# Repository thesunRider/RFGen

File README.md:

# RFGen

This is an open source DIY Square wave generator. There are two versions included: 
- Blue pill - (1Hz - 960Mhz)
- Atmega328p/Arduino (1Hz - 250Mhz)

### Schematics:

Arduino version

Bluepill version

- Si5351 - Channel A,B (1Khz - 250Mhz)
- CMT2119A - Channel E (only for bluepill version: 250Mhz - 960Mhz)

# Demo

Demo Video 

https://github.com/user-attachments/assets/bd40d5bd-5a4e-4a5a-9730-a542df9f6650

# Installation

- Upload 328p schematics for an Arduino based generator.
- Upload bluepill schematic for Bluepilll based generator.

> Gerber files attatched with kicad designs

# Usage

There is a bias tee included for these channels whose bias can be adjusted by the attached external potentiometer. 

Supply 9V on the power input, this is regulated to 5v by l7805

# Development

To program a soldered bluepill via USB kindly power off the device before connecting the USB. SInce UART pins are exposed you can program it via those headers too.

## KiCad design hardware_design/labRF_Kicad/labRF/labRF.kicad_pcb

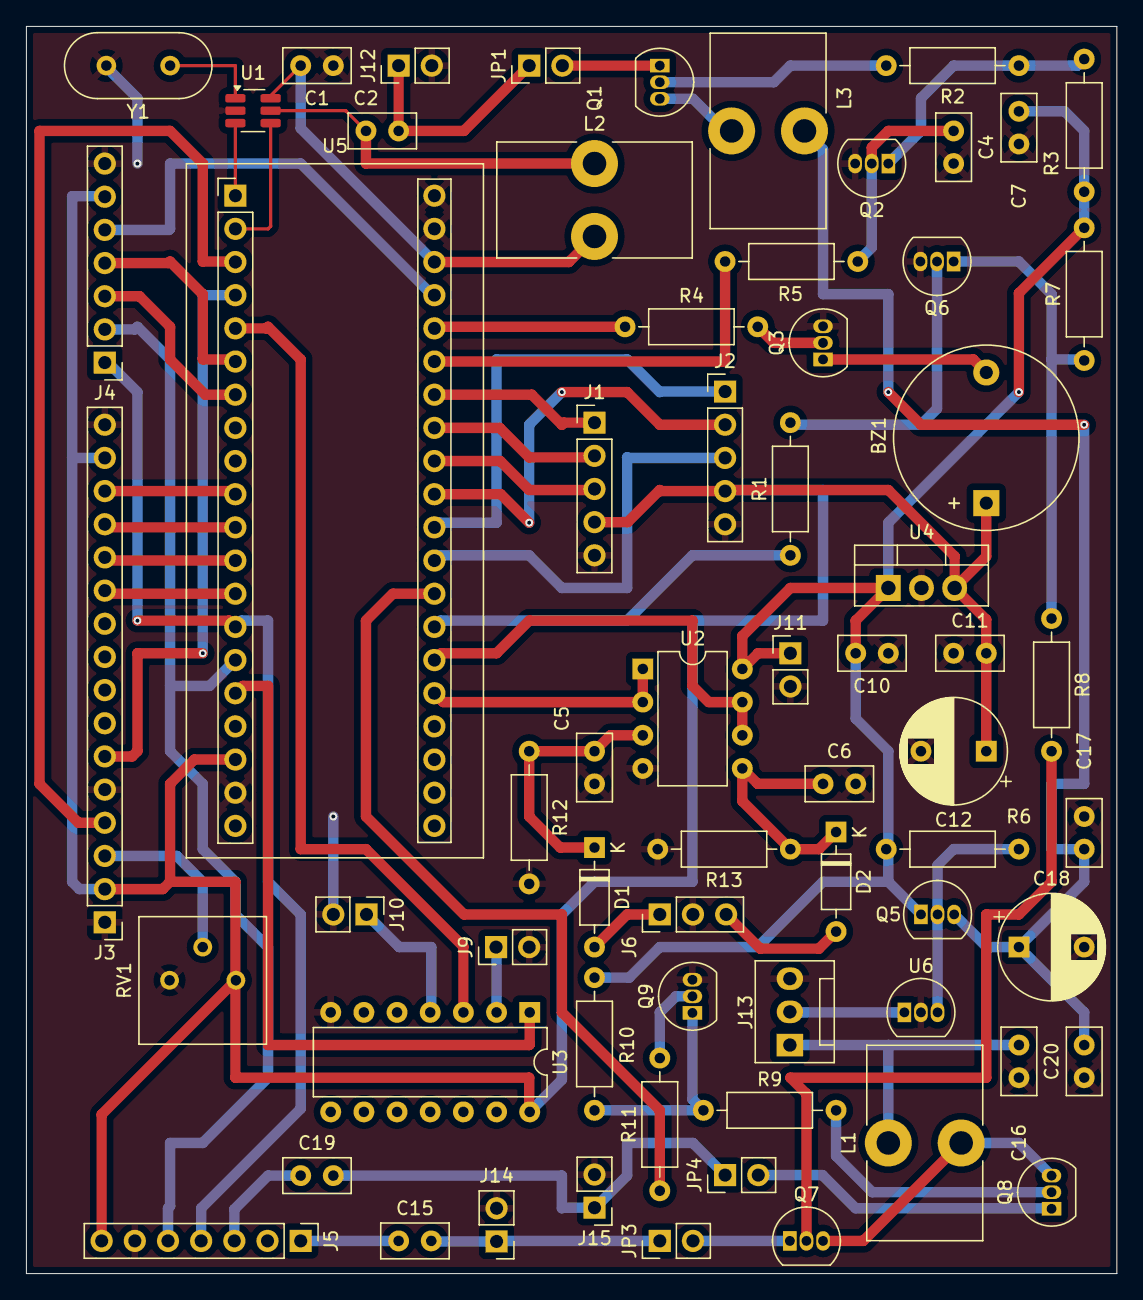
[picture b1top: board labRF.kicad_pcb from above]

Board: 2 copper layers, 83.5 x 95.5 mm, 66 parts (0 on the bottom side), 64 nets.

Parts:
BZ1: Buzzer; Buzzer_D14mm_H7mm_P10mm
C1, C2, C7, C11, C15, C16, C19: 100n; C_Disc_D5.0mm_W2.5mm_P2.50mm
C4, C5, C6, C10, C17, C20: 10n; C_Disc_D5.0mm_W2.5mm_P2.50mm
C12, C18: 100u; CP_Radial_D8.0mm_P5.00mm
D1, D2: 1N4148; D_DO-35_SOD27_P7.62mm_Horizontal
J1: select_rotary; PinHeader_1x05_P2.54mm_Vertical
J2: mode_rotary; PinHeader_1x05_P2.54mm_Vertical
J3: lcd_socket; PinHeader_1x16_P2.54mm_Vertical
J4: comms; PinHeader_1x07_P2.54mm_Vertical
J5: si5351; PinHeader_1x07_P2.54mm_Vertical
J6: Conn_01x03_Socket; PinHeader_1x03_P2.54mm_Vertical
J9: pwmD; PinHeader_1x02_P2.54mm_Vertical
J10: pwmC; PinHeader_1x02_P2.54mm_Vertical
J11: pwrIn; PinHeader_1x02_P2.54mm_Vertical
J12, J15: clk2; PinHeader_1x02_P2.54mm_Vertical
J13: bias_pot; FanPinHeader_1x03_P2.54mm_Vertical
J14: clk0; PinHeader_1x02_P2.54mm_Vertical
JP1, JP3, JP4: Jumper_2_Open; PinHeader_1x02_P2.54mm_Vertical
L1, L3: 100u; L_Toroid_Vertical_L14.7mm_W8.6mm_P5.58mm_Pulse_KM-1
L2: 200n; L_Toroid_Vertical_L14.7mm_W8.6mm_P5.58mm_Pulse_KM-1
Q1, Q7, Q8: BC557; TO-92_Inline
Q2, Q3, Q5, Q6, Q9: BC547; TO-92_Inline
R1, R2, R5, R8, R9, R11: 10k; R_Axial_DIN0207_L6.3mm_D2.5mm_P10.16mm_Horizontal
R3, R6, R7, R10: 1k; R_Axial_DIN0207_L6.3mm_D2.5mm_P10.16mm_Horizontal
R4: 2.2k; R_Axial_DIN0207_L6.3mm_D2.5mm_P10.16mm_Horizontal
R12, R13: 100k; R_Axial_DIN0207_L6.3mm_D2.5mm_P10.16mm_Horizontal
RV1: R_Potentiometer; Potentiometer_Bourns_3386P_Vertical
U1: CMT2119; SOT-23-6_Handsoldering
U2: LM358; DIP-8_W7.62mm
U3: 74HC04; DIP-14_W7.62mm
U4: L7805; TO-220-3_Vertical
U5: YAAJ_BluePill; YAAJ_BluePill_2
U6: TL431LP; TO-92_Inline
Y1: 26Mhz; Crystal_HC49-U_Vertical

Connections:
+3V3: C1.2, L2.2, U1.6 (VDD), U5.38 (3V3)
+5V: BZ1.1 (+), C11.2, C12.1, J1.4, J2.4, J3.2, J3.15, J4.6, J5.7, RV1.1, U3.14 (VCC), U4.3 (OUT), U5.18 (5V)
+9V: C7.2, C10.2, J11.1, Q5.1 (C), R3.2, R6.2, R7.2, R10.2, U2.8 (V+), U4.1 (IN)
GND: C1.1, C4.2, C5.2, C6.2, C7.1, C10.1, C11.1, C12.2, C16.1, C17.1, C18.2, C20.1, J1.5, J2.5, J3.1, J3.5, J3.16, J4.7, J5.6, J6.2, J9.2, J10.2, J11.2, J12.2, J13.3, J14.2, J15.2, Q2.3 (E), Q3.3 (E), Q6.3 (E), Q9.3 (E), R12.2, R13.2, RV1.3, U1.2 (GND), U2.4 (V-), U3.7 (GND), U4.2 (GND), U5.19 (GND), U5.39 (GND), U5.40 (GND), U6.2 (A), Y1.2
unnamed: BZ1.2 (-), Q3.1 (C)
unnamed: D1.2 (A), J6.1
unnamed: C5.1, D1.1 (K), R12.1, U2.3 (+)
unnamed: D2.2 (A), J6.3
unnamed: C6.1, D2.1 (K), R13.1, U2.5 (+)
unnamed: J9.1, U3.2
unnamed: J10.1, U3.4
unnamed: C2.2, J12.1, JP1.1 (A)
unnamed: C16.2, C17.2, C18.1, C20.2, J13.1, L1.1, L3.1, Q5.3 (E)
unnamed: J13.2, U6.1 (REF)
unnamed: C15.2, J14.1, JP3.1 (A)
unnamed: C19.2, J15.1, JP4.1 (A)
unnamed: JP1.2 (B), Q1.1 (C)
unnamed: JP3.2 (B), Q7.1 (C)
unnamed: JP4.2 (B), Q8.1 (C)
unnamed: Q1.2 (B), R2.2
unnamed: L3.2, Q1.3 (E)
unnamed: C4.1, Q2.2 (B), R5.2
unnamed: Q2.1 (C), R2.1, R3.1
unnamed: Q3.2 (B), R4.2
unnamed: Q5.2 (B), R6.1, U6.3 (K)
unnamed: Q6.2 (B), R1.2
unnamed: Q6.1 (C), R7.1, R8.1
unnamed: Q7.2 (B), R8.2
unnamed: L1.2, Q7.3 (E), Q8.3 (E)
unnamed: Q8.2 (B), R9.2
unnamed: Q9.2 (B), R11.2
unnamed: Q9.1 (C), R9.1, R10.1
unnamed: U1.1 (XTAL), Y1.1
adc1: U2.6 (-), U2.7, U5.26 (PA1)
adc2: U2.1, U2.2 (-), U5.25 (PA0)
bias1: R1.1, U5.27 (PA2)
bias2: R11.1, U5.28 (PA3)
bias3: R5.1, U5.35 (PB10)
buzz: R4.1, U5.36 (PB11)
chanE: C2.1, L2.1, U1.5 (RFO)
chanc: U3.3, U5.5 (PA8)
chand: U3.1, U5.16 (PB8)
clk0: C15.1, J5.1
clk2: C19.1, J5.3
lcd_D4: J3.11, U5.13 (PB5)
lcd_D5: J3.12, U5.12 (PB4)
lcd_D6: J3.13, U5.11 (PB3)
lcd_D7: J3.14, U5.10 (PA15)
lcd_contrast: J3.3, RV1.2
lcd_enb: J3.6, U5.4 (PB15)
lcd_rs: J3.4, U5.3 (PB14)
reset: J4.5, U5.37 (RST)
rotm_clk: J2.1, U5.30 (PA5)
rotm_dt: J2.2, U5.31 (PA6)
rotm_sw: J2.3, U5.29 (PA4)
rots_clk: J1.1, U5.34 (PB1)
rots_dt: J1.2, U5.33 (PB0)
rots_sw: J1.3, U5.32 (PA7)
rx: J4.3, U5.7 (PA10)
scl: J4.1, J5.4, U5.14 (PB6)
sda: J4.2, J5.5, U5.15 (PB7)
twi_clk: U1.4 (CLK), U5.2 (PB13)
twi_data: U1.3 (DATA), U5.1 (PB12)
tx: J4.4, U5.6 (PA9)

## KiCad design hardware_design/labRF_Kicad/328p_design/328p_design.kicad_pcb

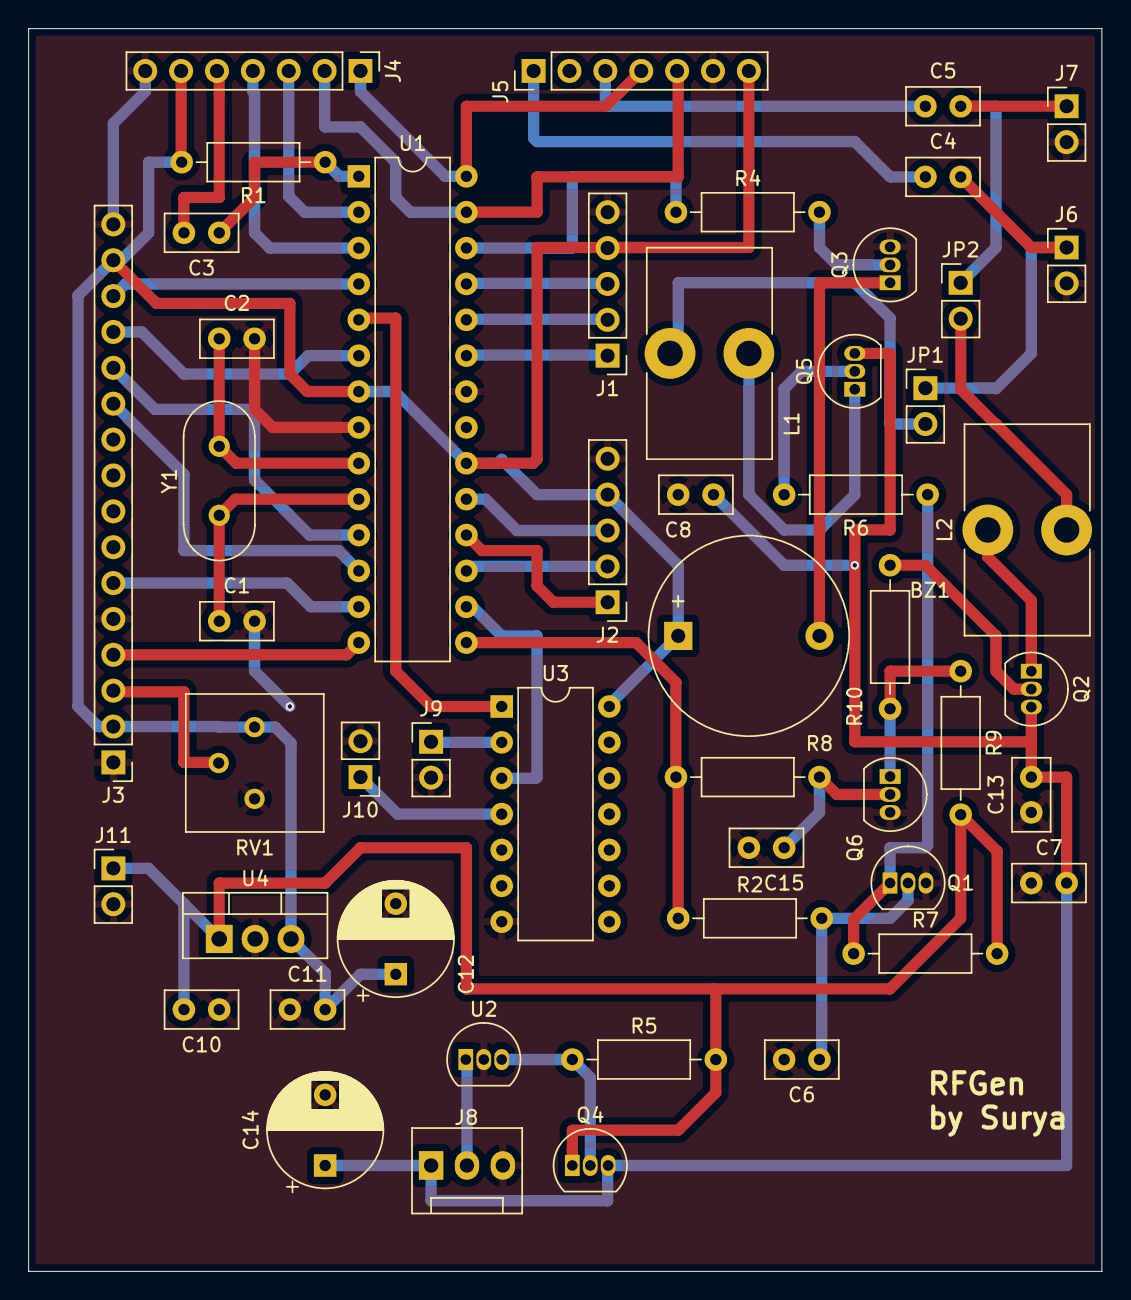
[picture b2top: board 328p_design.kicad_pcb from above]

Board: 2 copper layers, 76.0 x 88.0 mm, 51 parts (0 on the bottom side), 49 nets.

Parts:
BZ1: Buzzer; Buzzer_D14mm_H7mm_P10mm
C1, C2: 22p; C_Disc_D5.0mm_W2.5mm_P2.50mm
C3, C4, C5, C11, C13: 100n; C_Disc_D5.0mm_W2.5mm_P2.50mm
C6, C7, C8, C10, C15: 10n; C_Disc_D5.0mm_W2.5mm_P2.50mm
C12, C14: 100u; CP_Radial_D8.0mm_P5.00mm
J1: select_rotary; PinHeader_1x05_P2.54mm_Vertical
J2: mode_rotary; PinHeader_1x05_P2.54mm_Vertical
J3: lcd_socket; PinHeader_1x16_P2.54mm_Vertical
J4: comms; PinHeader_1x07_P2.54mm_Vertical
J5: si5351; PinHeader_1x07_P2.54mm_Vertical
J6: clk0; PinHeader_1x02_P2.54mm_Vertical
J7: clk2; PinHeader_1x02_P2.54mm_Vertical
J8: bias_pot; FanPinHeader_1x03_P2.54mm_Vertical
J9: pwmD; PinHeader_1x02_P2.54mm_Vertical
J10: pwmC; PinHeader_1x02_P2.54mm_Vertical
J11: pwrIn; PinHeader_1x02_P2.54mm_Vertical
JP1, JP2: Jumper_2_Open; PinHeader_1x02_P2.54mm_Vertical
L1, L2: 100u; L_Toroid_Vertical_L14.7mm_W8.6mm_P5.58mm_Pulse_KM-1
Q1, Q3, Q4, Q6: BC547; TO-92_Inline
Q2, Q5: BC557; TO-92_Inline
R1, R2, R6, R8, R10: 10k; R_Axial_DIN0207_L6.3mm_D2.5mm_P10.16mm_Horizontal
R4: 2.2k; R_Axial_DIN0207_L6.3mm_D2.5mm_P10.16mm_Horizontal
R5, R7, R9: 1k; R_Axial_DIN0207_L6.3mm_D2.5mm_P10.16mm_Horizontal
RV1: R_Potentiometer; Potentiometer_Bourns_3386P_Vertical
U1: ATmega328-P; DIP-28_W7.62mm
U2: TL431LP; TO-92_Inline
U3: 74HC04; DIP-14_W7.62mm
U4: L7805; TO-220-3_Vertical
Y1: 20Mhz; Crystal_HC49-U_Vertical

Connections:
+5V: BZ1.1 (+), C11.2, C12.1, J1.4, J2.4, J3.2, J3.15, J4.6, J5.7, R1.2, RV1.1, U1.7 (VCC), U1.20 (AVCC), U3.14 (VCC), U4.3 (OUT)
+9V: C10.2, J11.1, Q4.1 (C), R5.2, R7.2, R9.2, U4.1 (IN)
GND: C1.2, C2.2, C6.2, C7.1, C8.1, C10.1, C11.1, C12.2, C13.1, C14.2, C15.2, J1.5, J2.5, J3.1, J3.5, J3.16, J4.7, J5.6, J6.2, J7.2, J8.3, J9.2, J10.2, J11.2, Q1.3 (E), Q3.3 (E), Q6.3 (E), RV1.3, U1.8 (GND), U1.22 (GND), U2.2 (A), U3.7 (GND), U4.2 (GND)
unnamed: BZ1.2 (-), Q3.1 (C)
unnamed: C4.2, J6.1, JP1.1 (A)
unnamed: C5.2, J7.1, JP2.1 (A)
unnamed: C7.2, C8.2, C13.2, C14.1, J8.1, Q2.3 (E), Q4.3 (E), Q5.3 (E)
unnamed: J8.2, U2.1 (REF)
unnamed: J9.1, U3.2
unnamed: J10.1, U3.4
unnamed: JP1.2 (B), L1.2
unnamed: JP2.2 (B), L2.2
unnamed: C6.1, Q1.2 (B), R2.2
unnamed: Q1.1 (C), R6.1, R7.1
unnamed: Q2.2 (B), R10.2
unnamed: L2.1, Q2.1 (C)
unnamed: Q3.2 (B), R4.2
unnamed: Q4.2 (B), R5.1, U2.3 (K)
unnamed: Q5.2 (B), R6.2
unnamed: L1.1, Q5.1 (C)
unnamed: C15.1, Q6.2 (B), R8.2
unnamed: Q6.1 (C), R9.1, R10.1
unnamed: C2.1, U1.9 (XTAL1/PB6), Y1.2
unnamed: C1.1, U1.10 (XTAL2/PB7), Y1.1
unnamed: C3.1, R1.1, U1.1 (~RESET/PC6)
bias: R2.1, R8.1, U1.15 (PB1)
buzz: R4.1, U1.26 (PC3)
chanc: U1.16 (PB2), U3.3
chand: U1.5 (PD3), U3.1
clk0: C4.1, J5.1
clk2: C5.1, J5.3
lcd_D4: J3.11, U1.12 (PD6)
lcd_D5: J3.12, U1.11 (PD5)
lcd_D6: J3.13, U1.6 (PD4)
lcd_D7: J3.14, U1.4 (PD2)
lcd_contrast: J3.3, RV1.2
lcd_enb: J3.6, U1.13 (PD7)
lcd_rs: J3.4, U1.14 (PB0)
reset: C3.2, J4.5
rotm_clk: J2.1, U1.18 (PB4)
rotm_dt: J2.2, U1.17 (PB3)
rotm_sw: J2.3, U1.19 (PB5)
rots_clk: J1.1, U1.23 (PC0)
rots_dt: J1.2, U1.24 (PC1)
rots_sw: J1.3, U1.25 (PC2)
rx: J4.3, U1.2 (PD0)
scl: J4.1, J5.4, U1.28 (PC5)
sda: J4.2, J5.5, U1.27 (PC4)
tx: J4.4, U1.3 (PD1)

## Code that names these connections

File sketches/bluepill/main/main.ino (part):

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13 - rotm_sw
*/

#define TWI_DAT PB12
#define TWI_CLK PB13

#define BIAS_PIN1 PA2
#define BIAS_PIN2 PA3
#define BIAS_PIN3 PB10
#define BUZZ_PIN PB11
#define PWM_PIN2 PB8
#define PWM_PIN1 PA8

#define ROT_SELECT_CLK PB1
#define ROT_SELECT_DT PB0
#define ROT_SELECT_SW PA7

#define ROT_MODE_CLK PA5
#define ROT_MODE_DT PA6
#define ROT_MODE_SW PA4


// Pin mapping for the display:
const byte LCD_RS = PB14;
const byte LCD_E = PB15;
const byte LCD_D4 = PB5;
const byte LCD_D5 = PB4;
const byte LCD_D6 = PB3;
const byte LCD_D7 = PA15;
//LCD R/W pin to ground
//10K potentiometer wiper to VO
LiquidCrystal lcd(LCD_RS, LCD_E, LCD_D4, LCD_D5, LCD_D6, LCD_D7);
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
void click_select(EButton &btn) {
  switch_sel_status = 1;
  digitalWrite(BUZZ_PIN, HIGH);
  delay(buzz_duration);
  digitalWrite(BUZZ_PIN, LOW);
}

void click_mode(EButton &btn) {
  switch_mode_status = 1;
  digitalWrite(BUZZ_PIN, HIGH);
  delay(buzz_duration);
  digitalWrite(BUZZ_PIN, LOW);
}


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
    //play sound
    if (rselect_event || rmode_event && buzz_duration > 0) {
      digitalWrite(BUZZ_PIN, HIGH);
      delay(buzz_duration);
      digitalWrite(BUZZ_PIN, LOW);
    }

    if (rselect_event) {
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
    //play sound
    if (rselect_event || rmode_event && buzz_duration > 0) {
      digitalWrite(BUZZ_PIN, HIGH);
      delay(buzz_duration);
      digitalWrite(BUZZ_PIN, LOW);
    }

    if (was_clicked(MODE_SW, false) && option_selected == CHN_HFFREQ) {
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
    //play sound
    if (rselect_event || rmode_event && buzz_duration > 0) {
      digitalWrite(BUZZ_PIN, HIGH);
      delay(buzz_duration);
      digitalWrite(BUZZ_PIN, LOW);
    }

    if (was_clicked(MODE_SW, false) && option_selected == CHN_HFFREQ) {
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
    //play sound
    if (rselect_event || rmode_event && buzz_duration > 0) {
      digitalWrite(BUZZ_PIN, HIGH);
      delay(buzz_duration);
      digitalWrite(BUZZ_PIN, LOW);
    }

    if (was_clicked(SELECT_SW, false) && option_selected == ENABLE_C) {
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
    //play sound
    if (rselect_event || rmode_event && buzz_duration > 0) {
      digitalWrite(BUZZ_PIN, HIGH);
      delay(buzz_duration);
      digitalWrite(BUZZ_PIN, LOW);
    }

    if (was_clicked(SELECT_SW, false) && option_selected == ENABLE_C) {
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  pinMode(BIAS_PIN1, OUTPUT);
  pinMode(BIAS_PIN2, OUTPUT);
  pinMode(BIAS_PIN3, OUTPUT);
  pinMode(BUZZ_PIN, OUTPUT);

  digitalWrite(BIAS_PIN1, LOW);
  digitalWrite(BIAS_PIN2, LOW);
  digitalWrite(BIAS_PIN3, LOW);
  digitalWrite(BUZZ_PIN, HIGH);

  digitalWrite(PWM_PIN2, LOW);
  digitalWrite(PWM_PIN1, LOW);
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

  delay(SPLASH_DELAY);
  digitalWrite(BUZZ_PIN, LOW);
  lcd.clear();
}

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
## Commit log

2024-09-04 Added Tests
2024-09-04 created main 328p sketch
2024-09-04 added inits
2024-09-04 added main menu
2024-09-06 added freq adjuster
2024-09-06 added freq adjuster main
2024-09-08 Finished to Channel D
2024-09-10 Added main adjusters
2024-09-10 328p schematics added
2024-09-11 Finieshed PCB Design
2024-09-12 Upgraded Schematic to 9V reference
2024-09-13 Finished bluepill schematics
2024-09-13 Organised sections and uploaded schematics
2024-09-13 Linted 328p code
2024-09-14 Added blue pill code
2025-02-10 Added demo video
2025-02-10 Cropped demos
